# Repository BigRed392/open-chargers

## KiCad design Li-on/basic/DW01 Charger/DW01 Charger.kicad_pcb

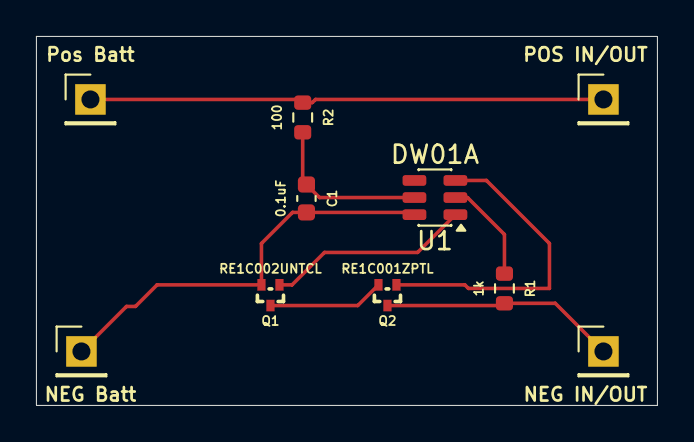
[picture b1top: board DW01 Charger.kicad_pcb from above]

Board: 2 copper layers, 34.5 x 20.5 mm, 10 parts (0 on the bottom side), 7 nets.

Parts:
C1: 0.1uF; C_0603_1608Metric
J1: Pos Batt; PinHeader_1x01_P2.54mm_Vertical
J2: NEG Batt; PinHeader_1x01_P2.54mm_Vertical
J3: POS IN/OUT; PinHeader_1x01_P2.54mm_Vertical
J4: NEG IN/OUT; PinHeader_1x01_P2.54mm_Vertical
Q1: RE1C002UNTCL; SC-89 SOT-490
Q2: RE1C001ZPTL; SC-89 SOT-490
R1: 1k; R_0603_1608Metric
R2: 100; R_0603_1608Metric
U1: DW01A; SOT-23-6

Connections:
unnamed: Q1.3 (D), Q2.2 (S)
unnamed: Q1.1 (G), U1.1 (OD)
unnamed: C1.2, Q1.2 (S), U1.6 (GND)
unnamed: Q2.3 (D), R1.2
unnamed: Q2.1 (G), U1.3 (OC)
unnamed: R1.1, U1.2 (CS)
unnamed: C1.1, R2.2, U1.5 (VCC)

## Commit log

2026-06-06 repo tidy up
